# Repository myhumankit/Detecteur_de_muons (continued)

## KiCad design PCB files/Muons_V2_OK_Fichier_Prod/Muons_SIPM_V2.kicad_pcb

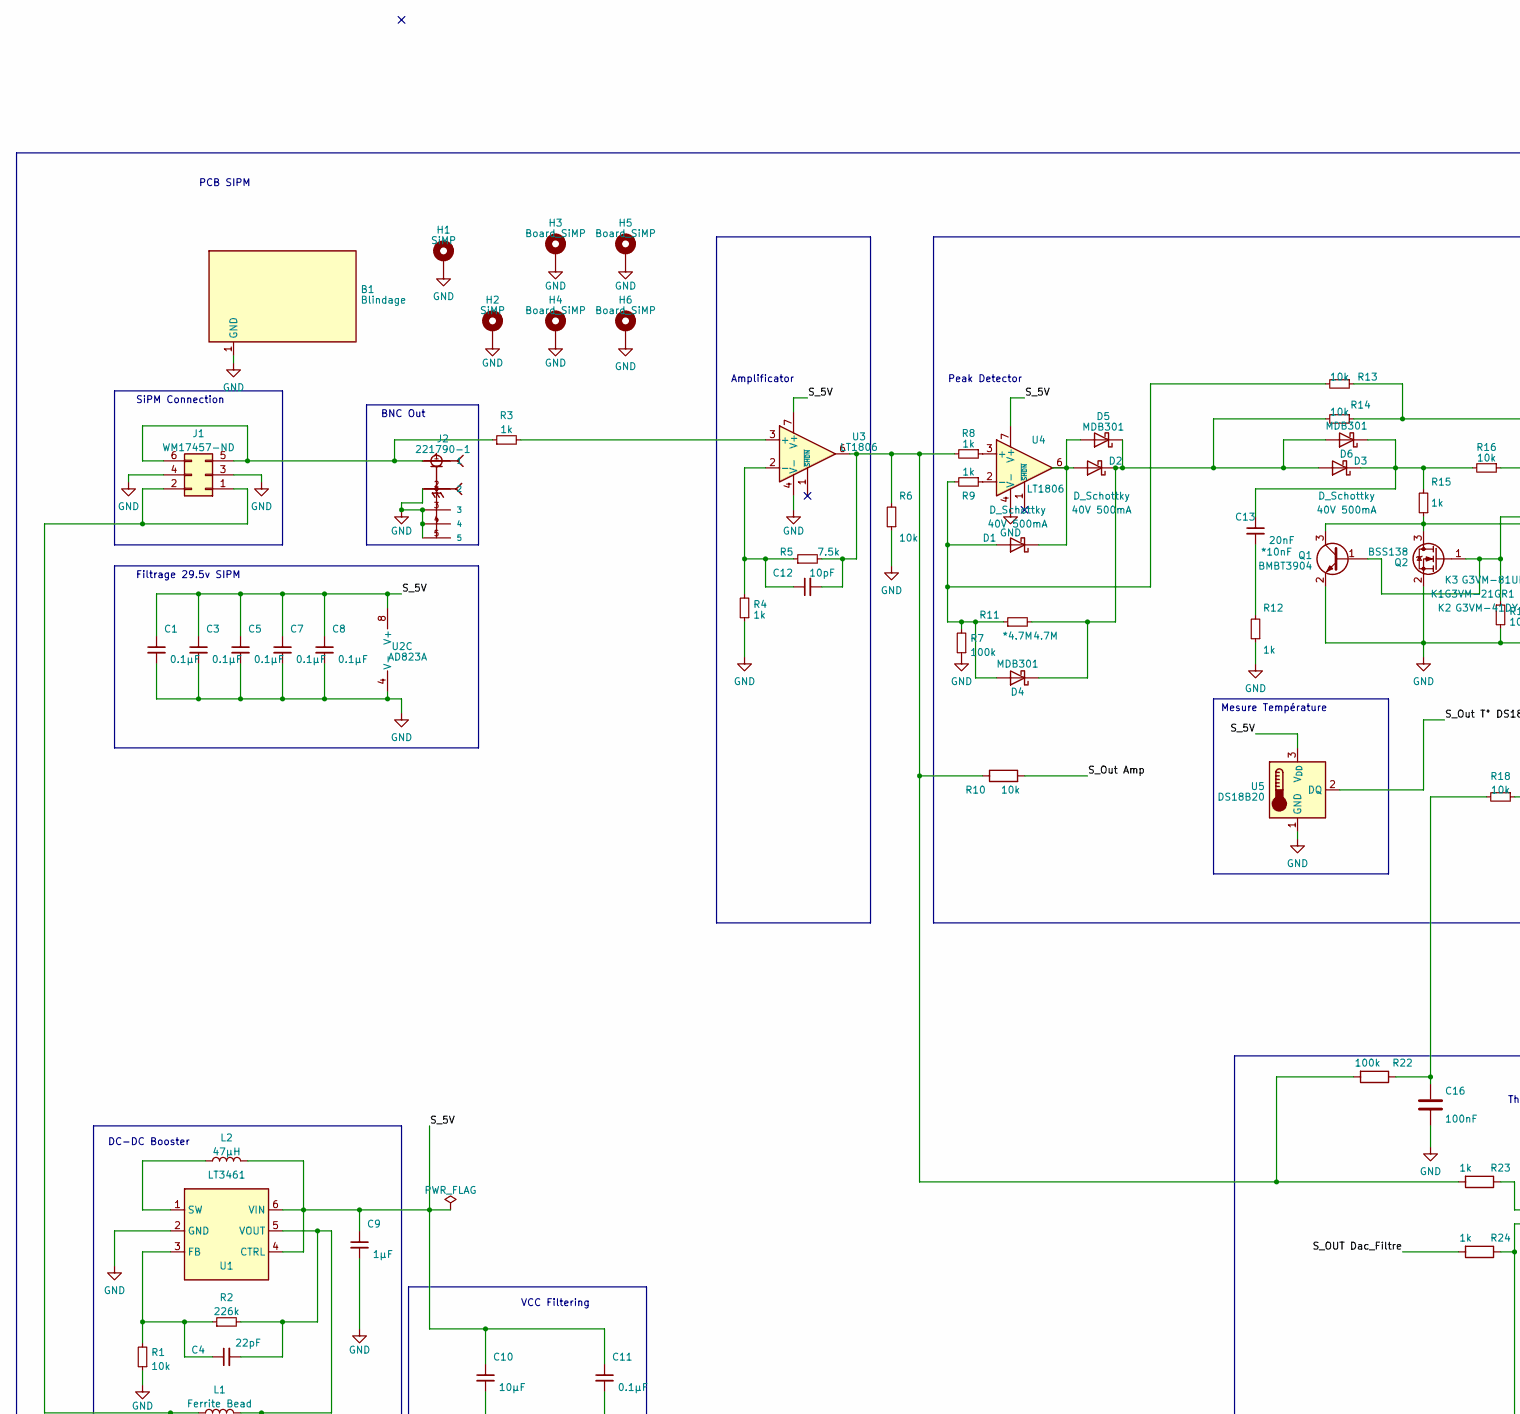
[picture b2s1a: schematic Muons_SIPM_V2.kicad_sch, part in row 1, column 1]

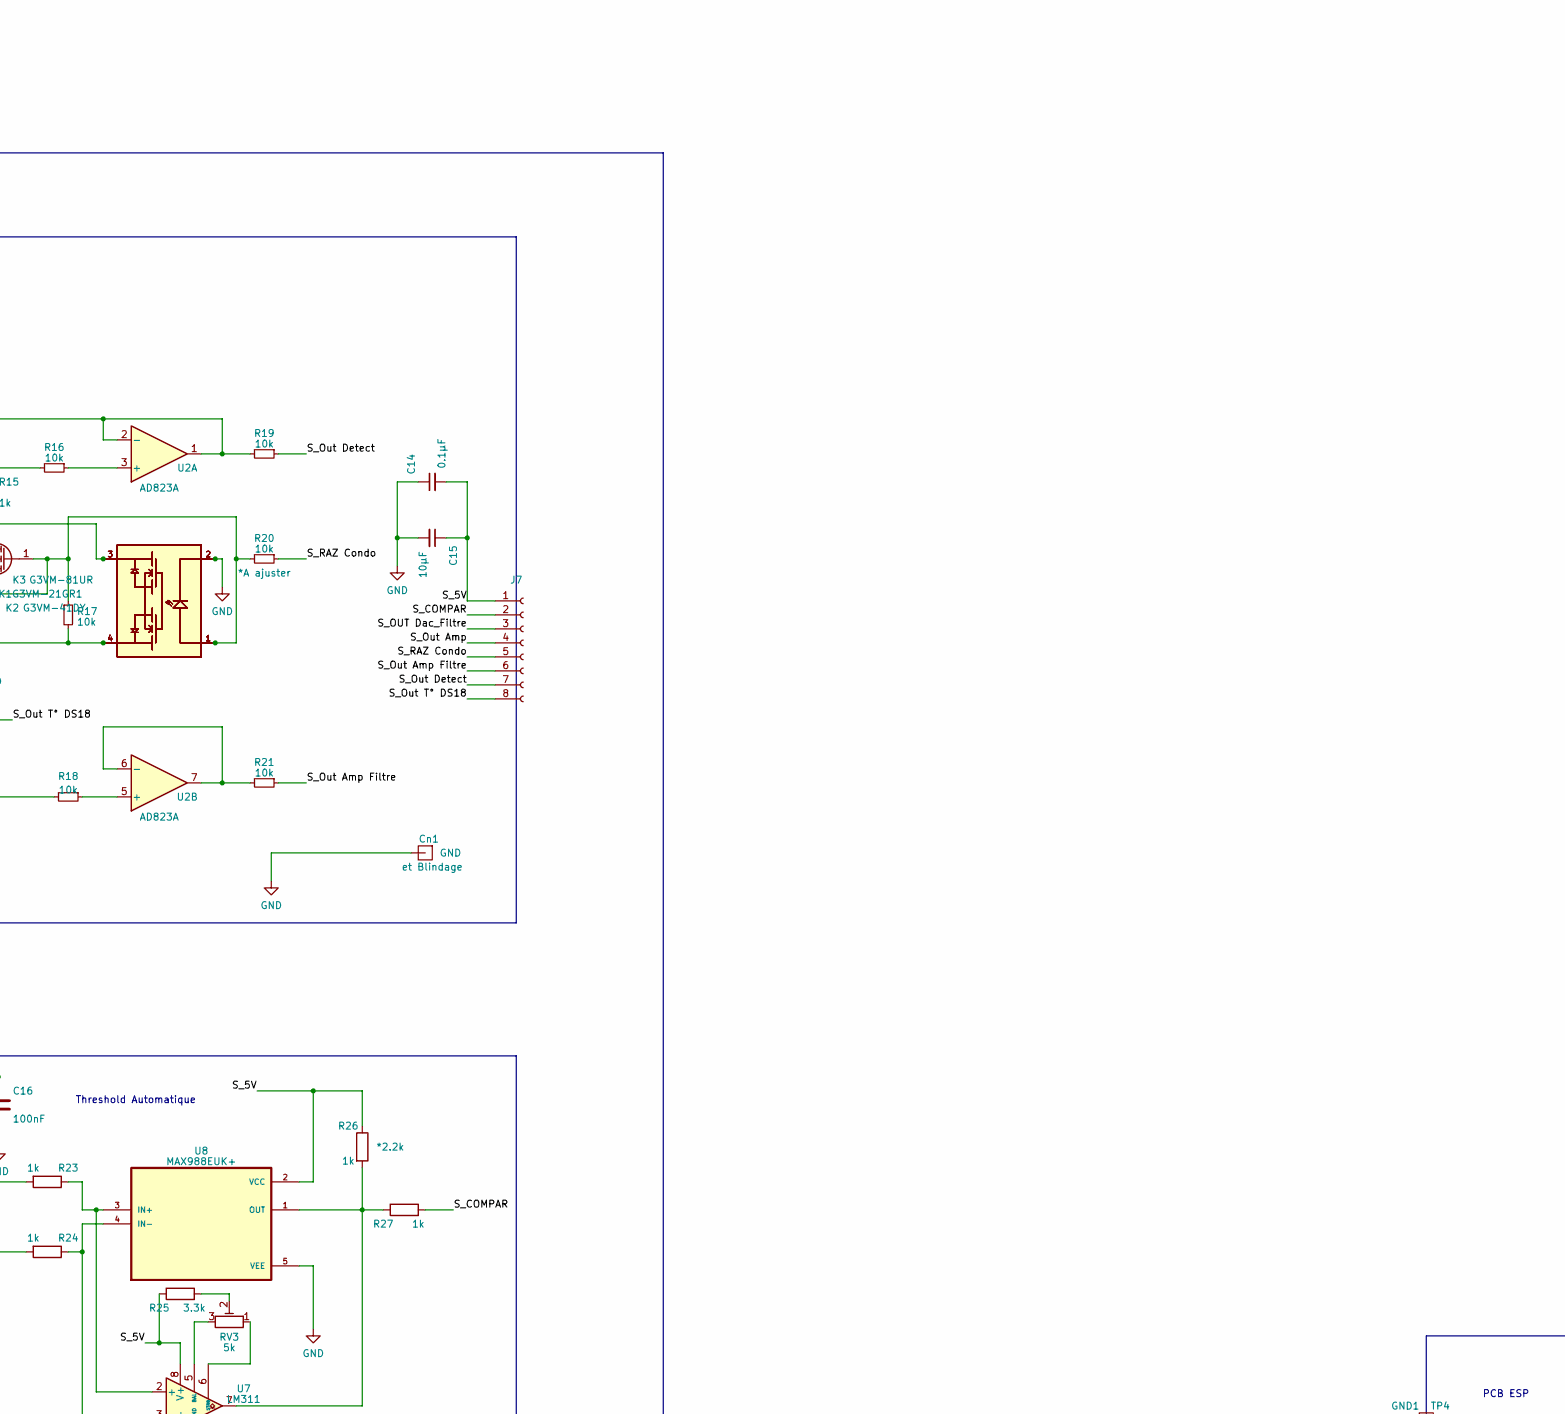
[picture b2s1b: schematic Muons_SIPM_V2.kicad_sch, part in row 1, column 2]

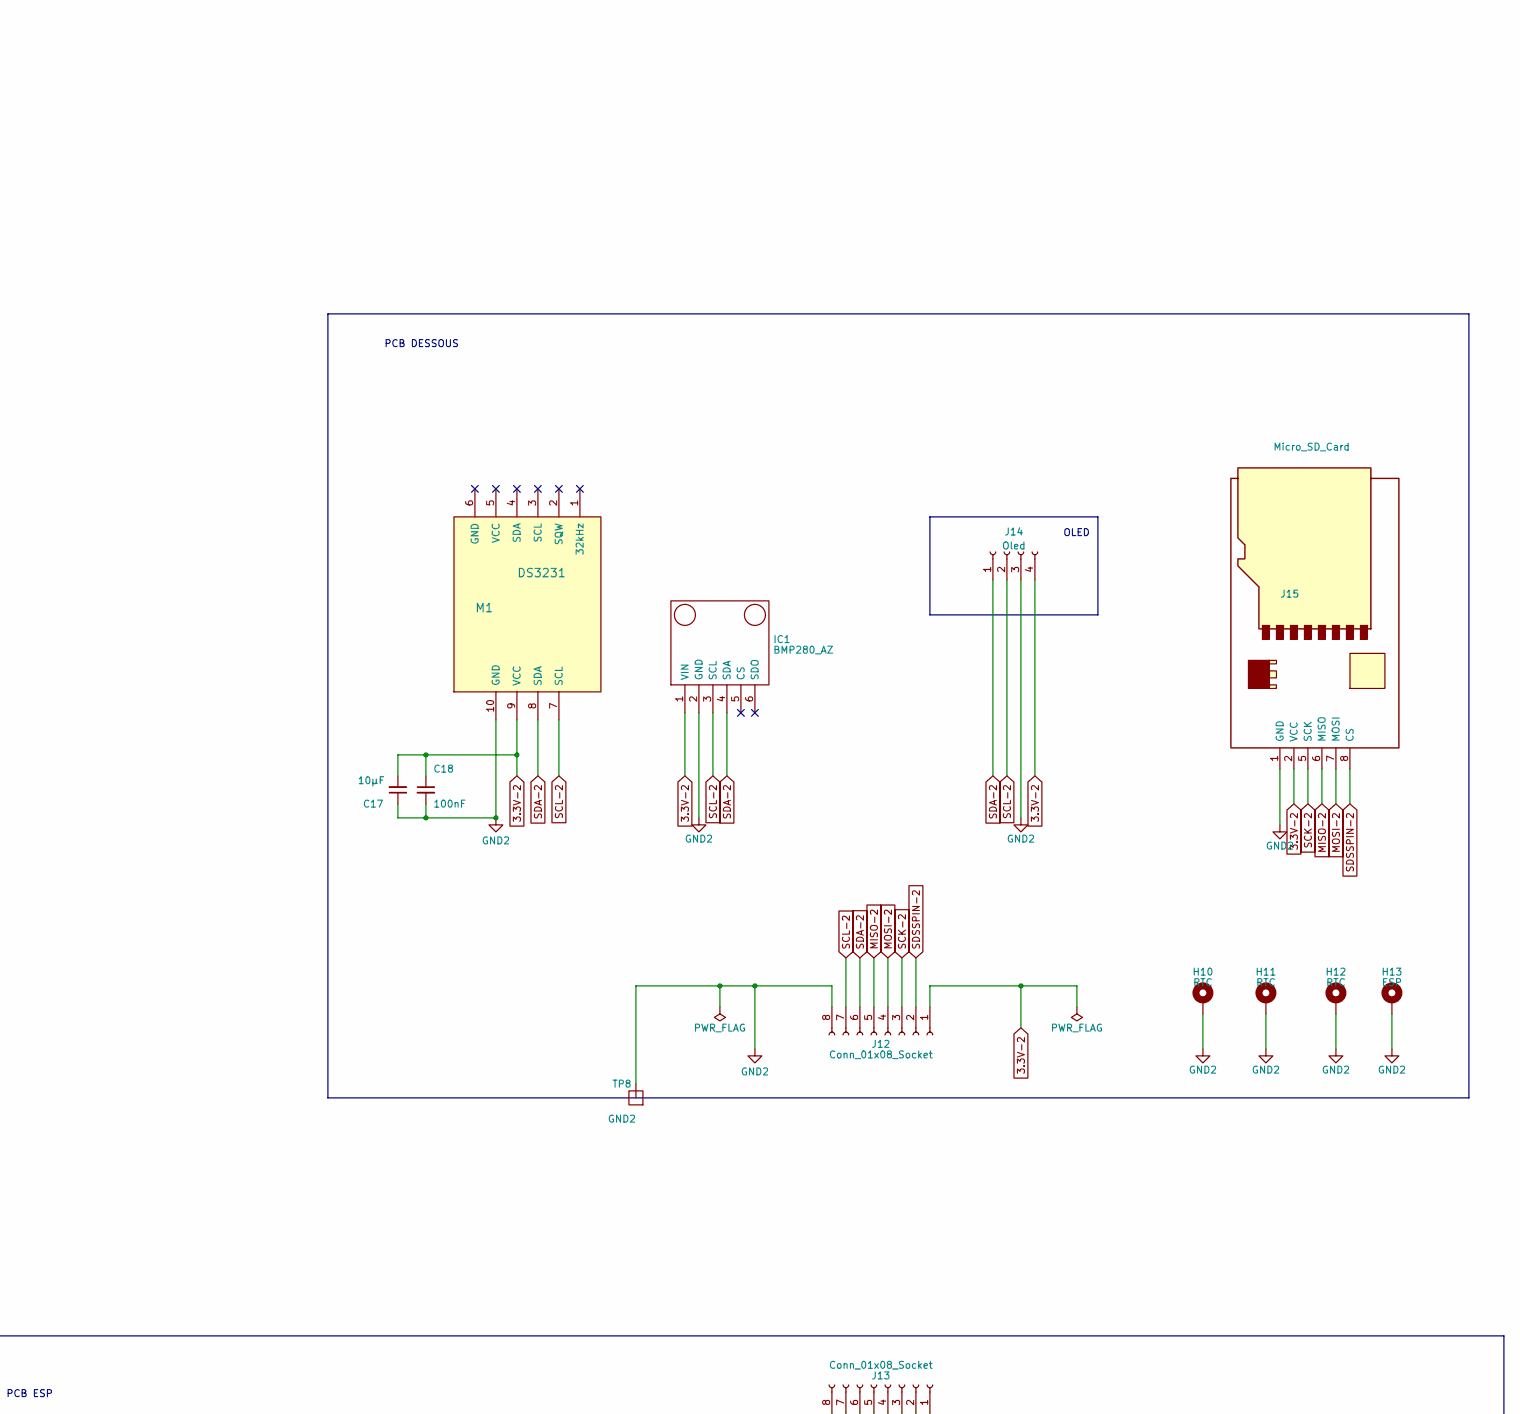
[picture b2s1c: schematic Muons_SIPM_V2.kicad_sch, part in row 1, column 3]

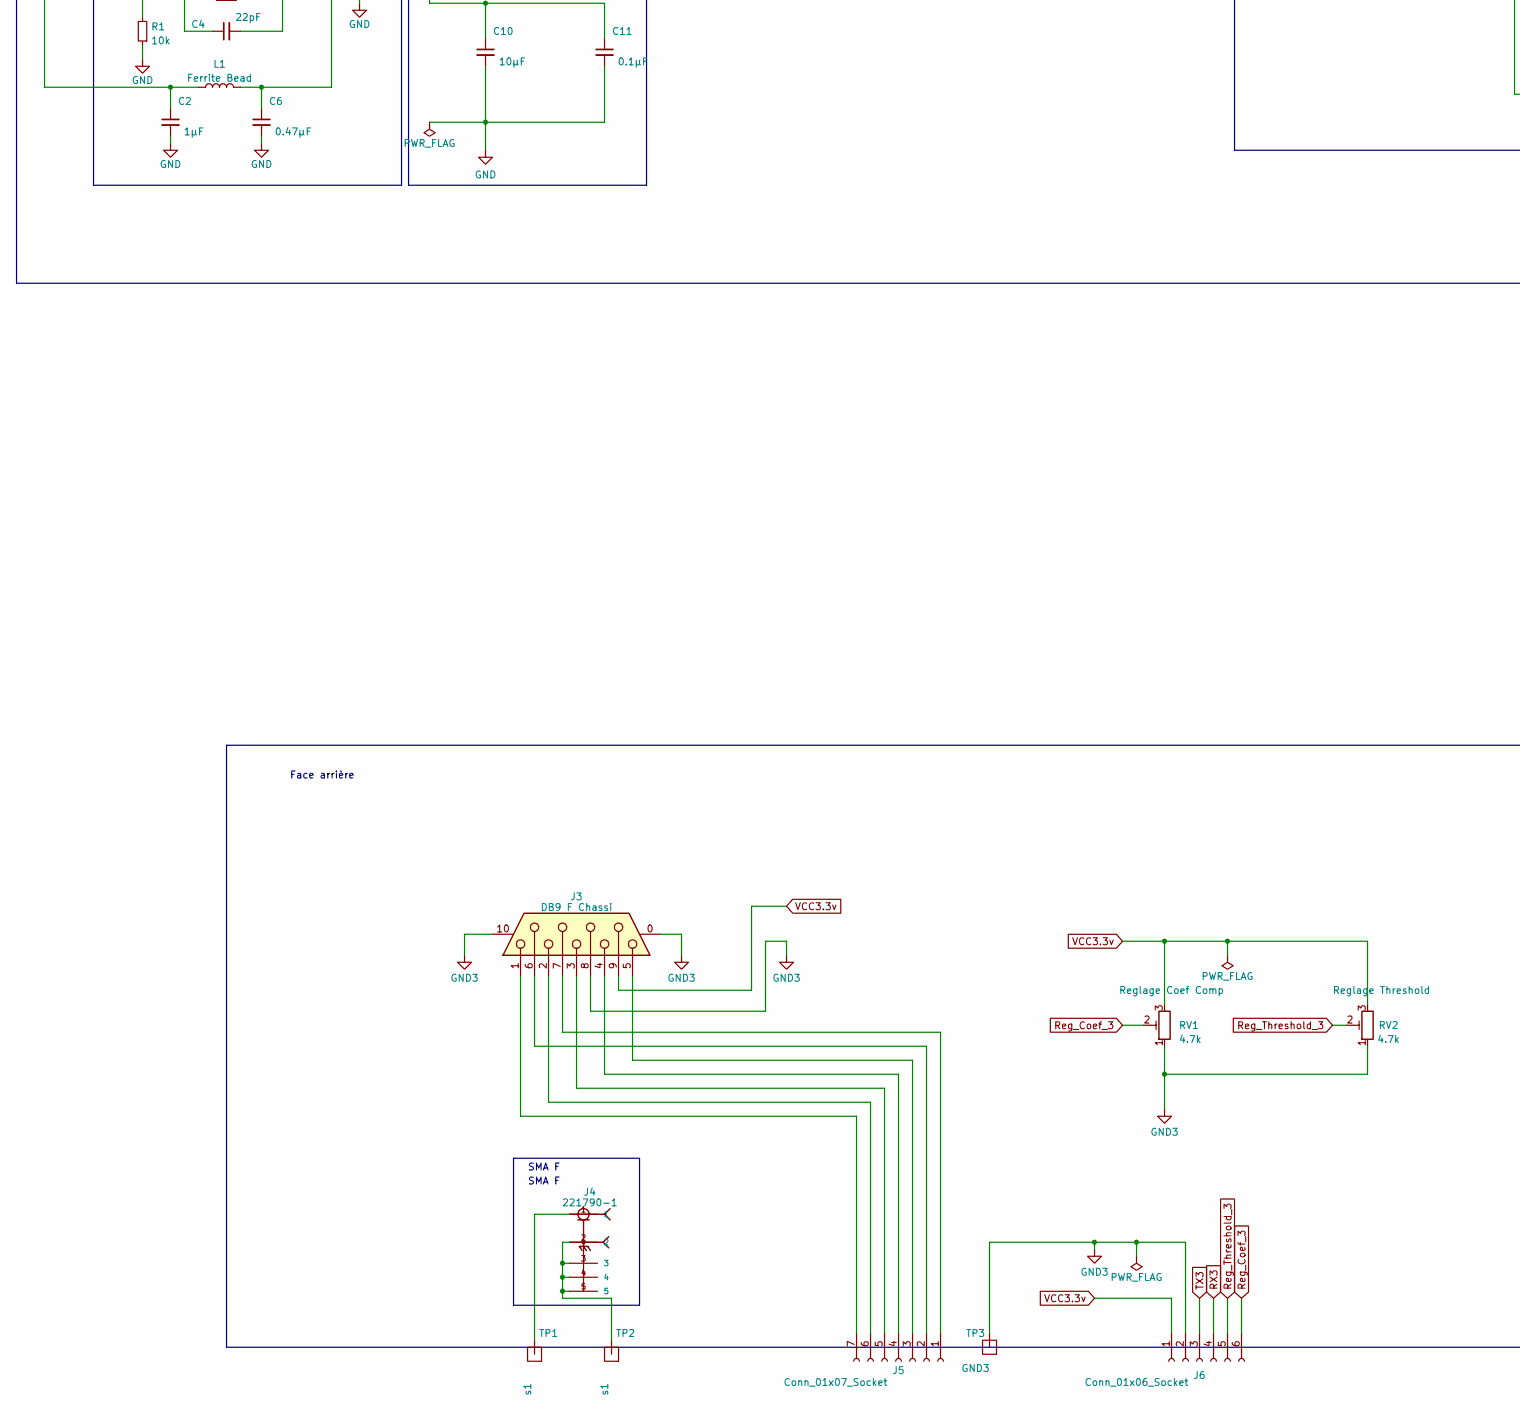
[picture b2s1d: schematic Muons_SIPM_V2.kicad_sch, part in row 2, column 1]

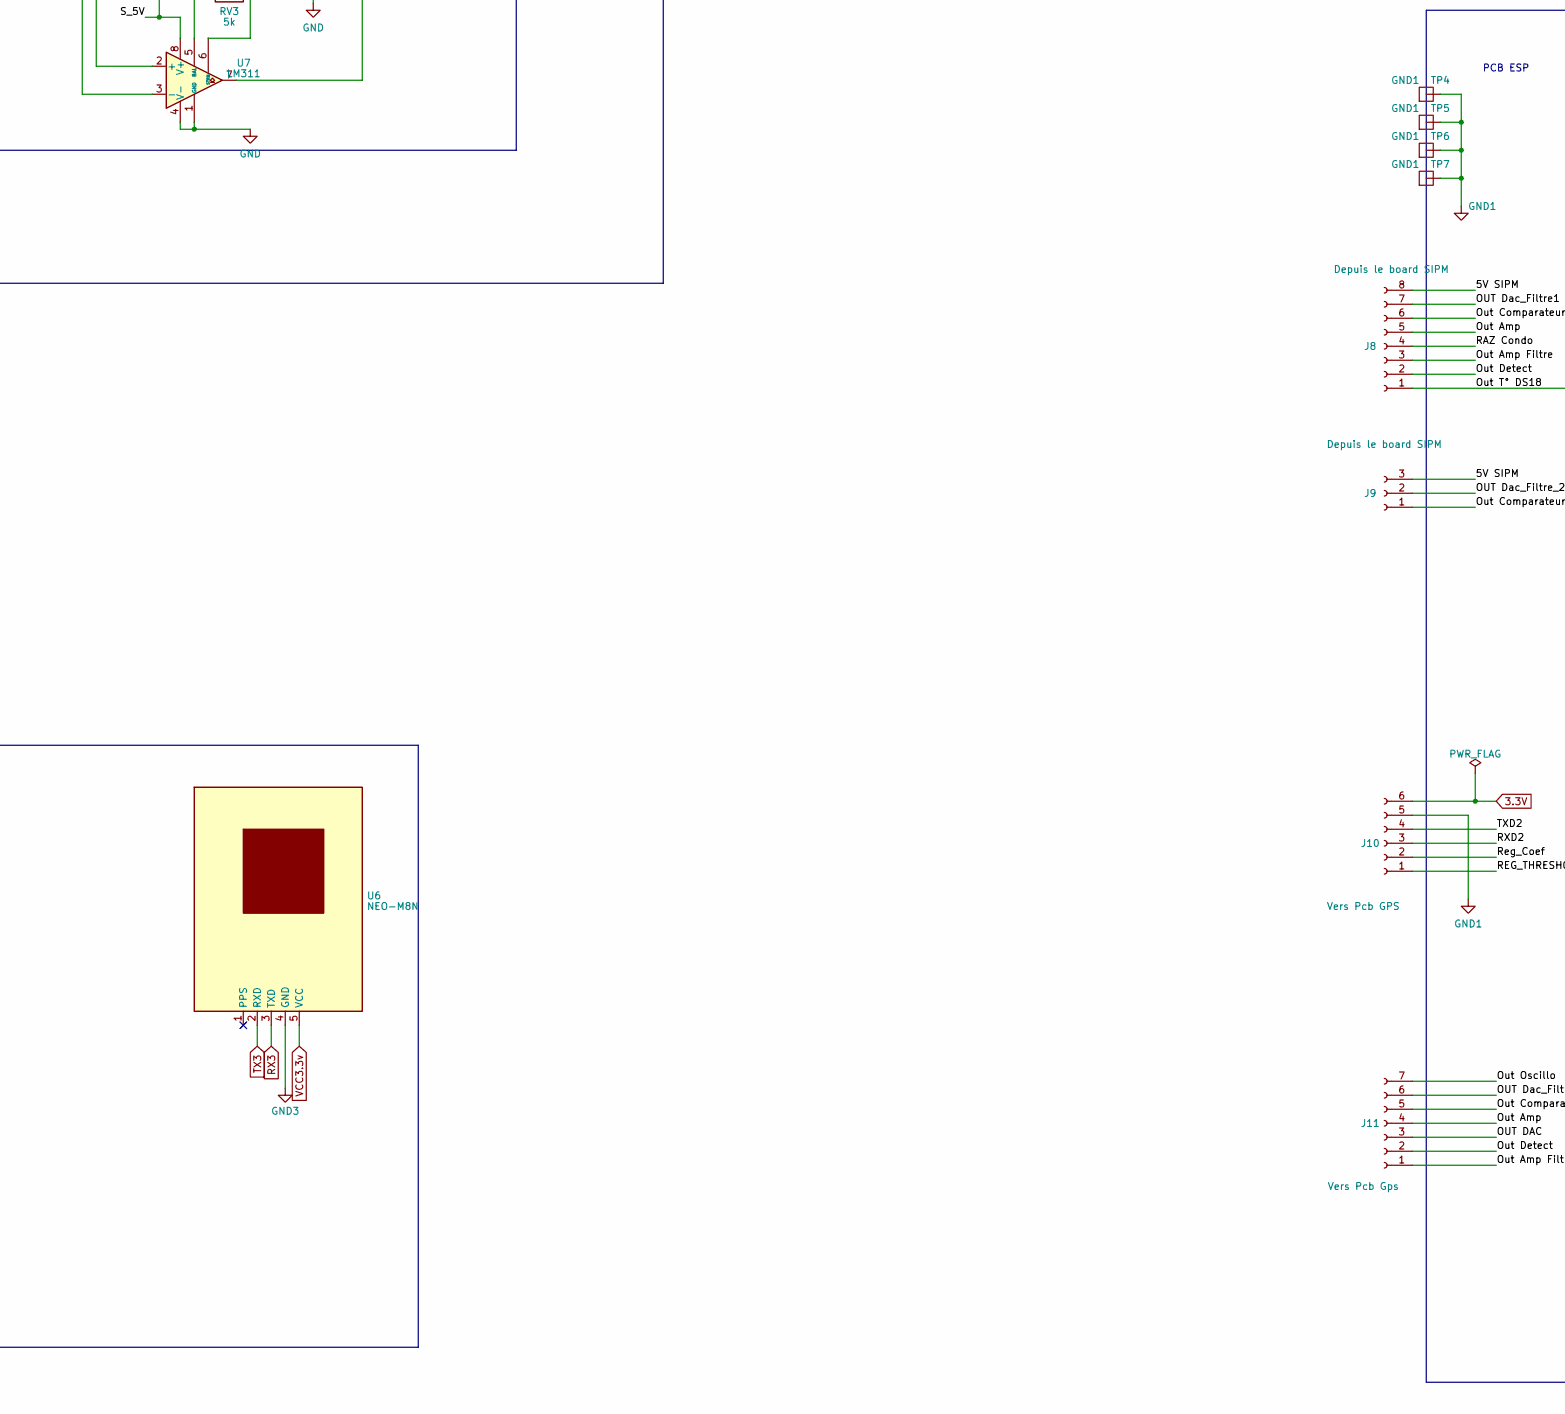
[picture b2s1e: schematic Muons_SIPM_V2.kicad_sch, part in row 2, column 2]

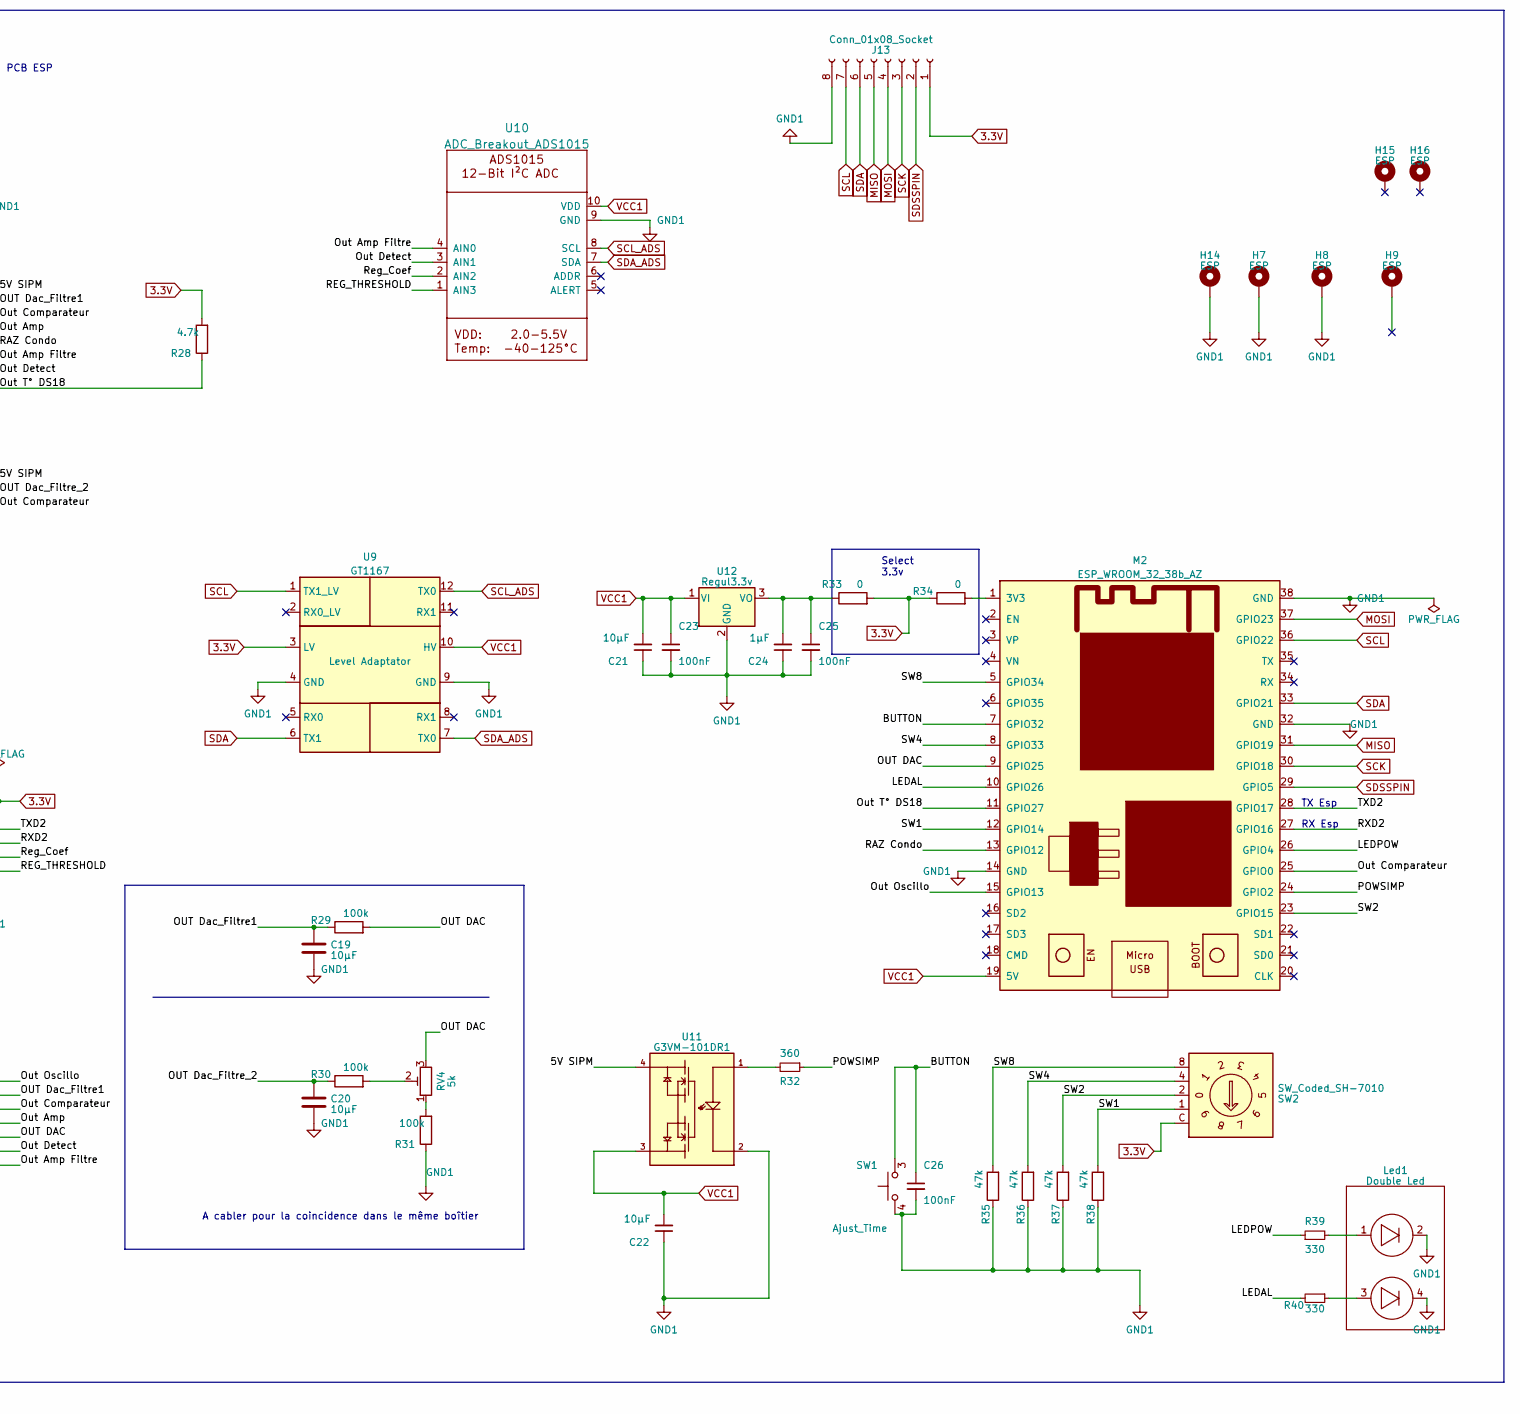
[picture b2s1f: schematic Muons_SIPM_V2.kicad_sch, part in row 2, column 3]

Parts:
B1: Blindage; Blindage_29.5
C1, C3, C5, C7, C8, C11, C14: 0.1µF; C_0805_Muons
C2, C9, C24: 1µF; C_0805_Muons
C4: 22pF; C_0805_Muons
C6: 0.47µF; C_0805_Muons
C10, C15, C17, C19, C20, C21, C22: 10µF; C_0805_Muons
C12: 10pF; C_0805_Muons
C13: 20nF; C_0805_Muons
C16, C18, C23, C25, C26: 100nF; C_0805_Muons
Cn1: GND; TestPoint_THTPad_4.75x3.7mm_Drill1.5mm
D1, D2, D3: D_Schottky; D_SOD-123
D4, D5, D6: MDB301; SOT-23
H1, H2: SiMP; MountingHole_2.2mm_M2_DIN965_Pad_TopBottom
H3, H4, H5, H6: Board_SiMP; MountingHole_2.2mm_M2_DIN965_Pad_TopBottom
H7, H8, H9, H13, H14: ESP; MountingHole_2.2mm_M2_DIN965_Pad_TopBottom
H10, H11, H12: RTC; MountingHole_2.2mm_M2_DIN965_Pad_TopBottom
H15, H16: ESP; MountingHole_2.2mm_M2
IC1: BMP280_AZ; Manufacturer_Part_Number BMP280_AZ
J1: WM17457-ND; PinSocket_2x03_P2.54mm_Vertical
J2, J4: 221790-1; TE_221790-1
J3: DB9 F Chassi; DSUB-9_Female_Horizontal_P2.77x2.84mm_EdgePinOffset4.94mm_H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
J5: Conn_01x07_Socket; Molex_KK-254_AE-6410-07A_1x07_P2.54mm_Vertical
J6: Conn_01x06_Socket; Molex_KK-254_AE-6410-06A_1x06_P2.54mm_Vertical
J7: Conn_01x08_Socket; Molex_KK-254_AE-6410-08A_1x08_P2.54mm_Vertical
J8: Depuis le board SIPM; Molex_KK-254_AE-6410-08A_1x08_P2.54mm_Vertical
J9: Depuis le board SIPM; Molex_KK-254_AE-6410-03A_1x03_P2.54mm_Vertical
J10: Vers Pcb GPS; Molex_KK-254_AE-6410-06A_1x06_P2.54mm_Vertical
J11: Vers Pcb Gps; Molex_KK-254_AE-6410-07A_1x07_P2.54mm_Vertical
J12: Conn_01x08_Socket; PinSocket_1x08_P2.54mm_Vertical
J13: Conn_01x08_Socket; PinHeader_1x08_P2.54mm_Vertical
J14: Oled; OLED_PCB
J15: Micro_SD_Card; SD-CARD_AZ
K1: G3VM-21GR1; PARTREV 0215
K2: G3VM-41DY; RELAY_G3VM-41DY; PARTREV 0215
K3: G3VM-81UR; PARTREV 0215
L1: Ferrite Bead; R_0805_2012Metric_Pad1.20x1.40mm_HandSolder
L2: 47µH; R_1210_3225Metric_Pad1.30x2.65mm_HandSolder
Led1: Double Led; Double_Led
M1: DS3231; REG_DS3231_2023
M2: ESP_WROOM_32_38b_AZ; MODULE_ESP32-DEVKITC
Q1: BMBT3904; SOT-323_SC-70
Q2: BSS138; SOT-23
R1, R6, R10, R13, R14, R16, R17, R18, R19, R20, R21: 10k; R_0805_Muons
R2: 226k; R_0805_Muons
R3, R4, R8, R9, R12, R15, R23, R24, R26, R27: 1k; R_0805_Muons
R5: 7.5k; R_0805_Muons
R7, R22, R29, R30, R31: 100k; R_0805_Muons
R11: 4.7M; R_0805_Muons
R25: 3.3k; R_0805_Muons
R28: 4.7k; R_0805_Muons
R32: 360; R_0805_Muons
R33, R34: 0; R_Shunt_0805_Muons
R35, R36, R37, R38: 47k; R_0805_Muons
R39, R40: 330; R_0805_Muons
RV1, RV2: 4.7k; Potentiometer_Bourns_3005_Horizontal
RV3, RV4: 5k; Potentiometer_Bourns_3314G_Vertical
SW1: Ajust_Time; SW_Tactile_SPST_Angled_PTS645Vx83-2LFS
SW2: SW_Coded_SH-7010; Nidec_Copal_SC-1110
TP1, TP2: s1; TestPoint_THTPad_4.75x3.7mm_Drill1.5mm
TP3: GND3; TestPoint_THTPad_4.75x3.7mm_Drill1.5mm
TP4, TP5, TP6, TP7: GND1; TestPoint_THTPad_4.75x3.7mm_Drill1.5mm
TP8: GND2; TestPoint_THTPad_4.75x3.7mm_Drill1.5mm
U1: LT3461; TSOT-23-6
U2: AD823A; SOIC-8_3.9x4.9mm_P1.27mm
U3, U4: LT1806; SOIC-8_3.9x4.9mm_P1.27mm
U5: DS18B20; TO-92_Inline
U6: NEO-M8N; GPS_NEO8
U7: LM311; SOIC-8_3.9x4.9mm_P1.27mm
U8: MAX988EUK+; SOT95P280X145-5N
U9: GT1167; DIP-12_Convertisseur
U10: ADC_Breakout_ADS1015; ADS1115_Small_BreakBord
U11: G3VM-101DR1; G3VM-21GR1; PARTREV 0215
U12: Regul3.3v; Regulateur

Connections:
3.3V: J10.6, J13.1, R28.2, R33.2, R34.1, SW2.C, U9.3 (LV)
3.3V-2: C17.2, C18.1, IC1.1 (VIN), J12.1, J14.4, J15.2 (VCC), M1.9 (VCC)
/5V SIPM: J8.8, J9.3, U11.4
/BUTTON: C26.1, M2.7 (GPIO32), SW1.3 (B), SW1.4 (B)
/LEDAL: M2.10 (GPIO26), R40.2
/LEDPOW: M2.26 (GPIO4), R39.1
/OUT DAC: J11.3, M2.9 (GPIO25), R29.2, RV4.3
/OUT Dac_Filtre1: C19.1, J8.7, J11.6, R29.1
/OUT Dac_Filtre_2: C20.1, J9.2, R30.1
/Out Amp: J8.5, J11.4
/Out Amp Filtre: J8.3, J11.1, U10.4 (AIN0)
/Out Comparateur: J8.6, J9.1, J11.5, M2.25 (GPIO0)
/Out Detect: J8.2, J11.2, U10.3 (AIN1)
/Out Oscillo: J11.7, M2.15 (GPIO13)
/Out T° DS18: J8.1, M2.11 (GPIO27), R28.1
/POWSIMP: M2.24 (GPIO2), R32.1
/RAZ Condo: J8.4, M2.13 (GPIO12)
/REG_THRESHOLD: J10.1, U10.1 (AIN3)
/RXD2: J10.3, M2.27 (GPIO16)
/Reg_Coef: J10.2, U10.2 (AIN2)
/SW1: M2.12 (GPIO14), R38.2, SW2.1
/SW2: M2.23 (GPIO15), R37.2, SW2.2
/SW4: M2.8 (GPIO33), R36.2, SW2.4
/SW8: M2.5 (GPIO34), R35.2, SW2.8
/S_5V: C1.1, C3.1, C5.1, C7.1, C8.1, C9.1, C10.1, C11.1, C14.2, C15.1, J7.1, L2.2, R25.1, R26.1, U1.4 (CTRL), U1.6 (VIN), U2.8 (V+), U3.7 (V+), U4.7 (V+), U5.3 (V_{DD}), U7.8 (V+), U8.2 (VCC)
/S_COMPAR: J7.2, R27.2
/S_OUT Dac_Filtre: J7.3, R24.2
/S_Out Amp: J7.4, R10.2
/S_Out Amp Filtre: J7.6, R21.1
/S_Out Detect: J7.7, R19.1
/S_Out T° DS18: J7.8, U5.2 (DQ)
/S_RAZ Condo: J7.5, R20.1
/TXD2: J10.4, M2.28 (GPIO17)
GND: B1.1 (GND), C1.2, C2.2, C3.2, C5.2, C6.2, C7.2, C8.2, C9.2, C10.2, C11.2, C14.1, C15.2, C16.2, Cn1.1, H1.1, H2.1, H3.1, H4.1, H5.1, H6.1, J1.3, J1.4, J2.2, J2.3, J2.4, J2.5, K1.2, K1.4, K2.2, K2.4, K3.2, K3.4, Q1.2 (E), Q2.2 (S), R1.1, R4.1, R6.1, R7.1, R12.1, R17.2, U1.2 (GND), U2.4 (V-), U3.4 (V-), U4.4 (V-), U5.1 (GND), U7.1 (GND), U7.4 (V-), U8.5 (VEE)
GND1: C19.2, C20.2, C21.1, C22.1, C23.2, C24.1, C25.2, C26.2, H7.1, H8.1, H14.1, J10.5, J13.8, Led1.2 (K1), Led1.4 (K2), M2.14 (GND), M2.32 (GND), M2.38 (GND), R31.1, R35.1, R36.1, R37.1, R38.1, SW1.1 (A), SW1.2 (A), TP4.1, TP5.1, TP6.1, TP7.1, U9.4 (GND), U9.9 (GND), U10.9 (GND), U11.2, U12.2 (GND)
GND2: C17.1, C18.2, H10.1, H11.1, H12.1, H13.1, IC1.2 (GND), J12.8, J14.3, J15.1 (GND), M1.10 (GND), TP8.1
GND3: J3.0 (PAD), J3.8, J3.10 (PAD), J6.2, RV1.1, RV2.1, TP3.1, U6.4 (GND)
MISO: J13.5, M2.31 (GPIO19)
MISO-2: J12.5, J15.6 (MISO)
MOSI: J13.4, M2.37 (GPIO23)
MOSI-2: J12.4, J15.7 (MOSI)
unnamed: C12.2, R5.2, R6.2, R8.2, R10.1, R22.2, R23.2, U3.6
unnamed: C13.2, R12.2
unnamed: C16.1, R18.2, R22.1
unnamed: D1.2 (A), D4.1 (A), R7.2, R9.2, R11.1, R13.2
unnamed: D1.1 (K), D2.2 (A), D5.1 (A), U4.6
unnamed: D2.1 (K), D3.2 (A), D4.3 (K), D5.3 (K), D6.1 (A), R11.2, R14.2
unnamed: C13.1, D3.1 (K), D6.3 (K), R15.2, R16.2
unnamed: C2.1, J1.1, J1.2, L1.1
unnamed: J1.5, J1.6, J2.1, R3.1
unnamed: J4.1, TP1.1
unnamed: J4.2, J4.3, J4.4, J4.5, TP2.1
unnamed: J3.7, J5.1
unnamed: J3.6, J5.2
unnamed: J3.5, J5.3
unnamed: J3.4, J5.4
unnamed: J3.3, J5.5
unnamed: J3.2, J5.6
unnamed: J3.1, J5.7
unnamed: Led1.1 (A1), R39.2
unnamed: Led1.3 (A2), R40.1
unnamed: M2.1 (3V3), R34.2
unnamed: K1.1, K2.1, K3.1, Q1.1 (B), Q2.1 (G), R17.1, R20.2
unnamed: K1.3, K2.3, K3.3, Q1.3 (C), Q2.3 (D), R15.1
unnamed: R25.2, RV3.2
unnamed: R30.2, RV4.2
unnamed: R31.2, RV4.1
unnamed: R32.2, U11.1
unnamed: C4.1, R1.2, R2.1, U1.3 (FB)
unnamed: L2.1, U1.1 (SW)
unnamed: C4.2, C6.1, L1.2, R2.2, U1.5 (VOUT)
unnamed: R16.1, U2.3 (+)
unnamed: R13.1, R14.1, R19.2, U2.1, U2.2 (-)
unnamed: R18.1, U2.5 (+)
unnamed: R21.2, U2.6 (-), U2.7
unnamed: R3.2, U3.3 (+)
unnamed: C12.1, R4.2, R5.1, U3.2 (-)
unnamed: R8.1, U4.3 (+)
unnamed: R9.1, U4.2 (-)
unnamed: R23.1, U7.2 (+), U8.3 (IN+)
unnamed: R24.1, U7.3 (-), U8.4 (IN-)
unnamed: RV3.3, U7.5 (BAL)
unnamed: RV3.1, U7.6 (STRB)
unnamed: R26.2, R27.1, U7.7, U8.1 (OUT)
unnamed: C24.2, C25.1, R33.1, U12.3 (VO)
RX3: J6.4, U6.3 (TXD)
Reg_Coef_3: J6.6, RV1.2
Reg_Threshold_3: J6.5, RV2.2
SCK: J13.3, M2.30 (GPIO18)
SCK-2: J12.3, J15.5 (SCK)
SCL: J13.7, M2.36 (GPIO22), U9.1 (TX1_LV)
SCL-2: IC1.3 (SCL), J12.7, J14.2, M1.7 (SCL)
SCL_ADS: U9.12 (TX0), U10.8 (SCL)
SDA: J13.6, M2.33 (GPIO21), U9.6 (TX1)
SDA-2: IC1.4 (SDA), J12.6, J14.1, M1.8 (SDA)
SDA_ADS: U9.7 (TX0), U10.7 (SDA)
SDSSPIN: J13.2, M2.29 (GPIO5)
SDSSPIN-2: J12.2, J15.8 (CS)
TX3: J6.3, U6.2 (RXD)
VCC1: C21.2, C22.2, C23.1, M2.19 (5V), U9.10 (HV), U10.10 (VDD), U11.3, U12.1 (VI)
VCC3.3v: J3.9, J6.1, RV1.3, RV2.3, U6.5 (VCC)

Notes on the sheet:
VCC Filtering
Face arrière
Peak Detector
OLED
PCB DESSOUS
Select 3.3v
PCB ESP
A cabler pour la coincidence dans le même boîtier
PCB SIPM
Mesure Température
RX Esp
SMA F
Filtrage 29.5v SIPM
TX Esp
SiPM Connection
DC-DC Booster
Amplificator
Threshold Automatique
BNC Out

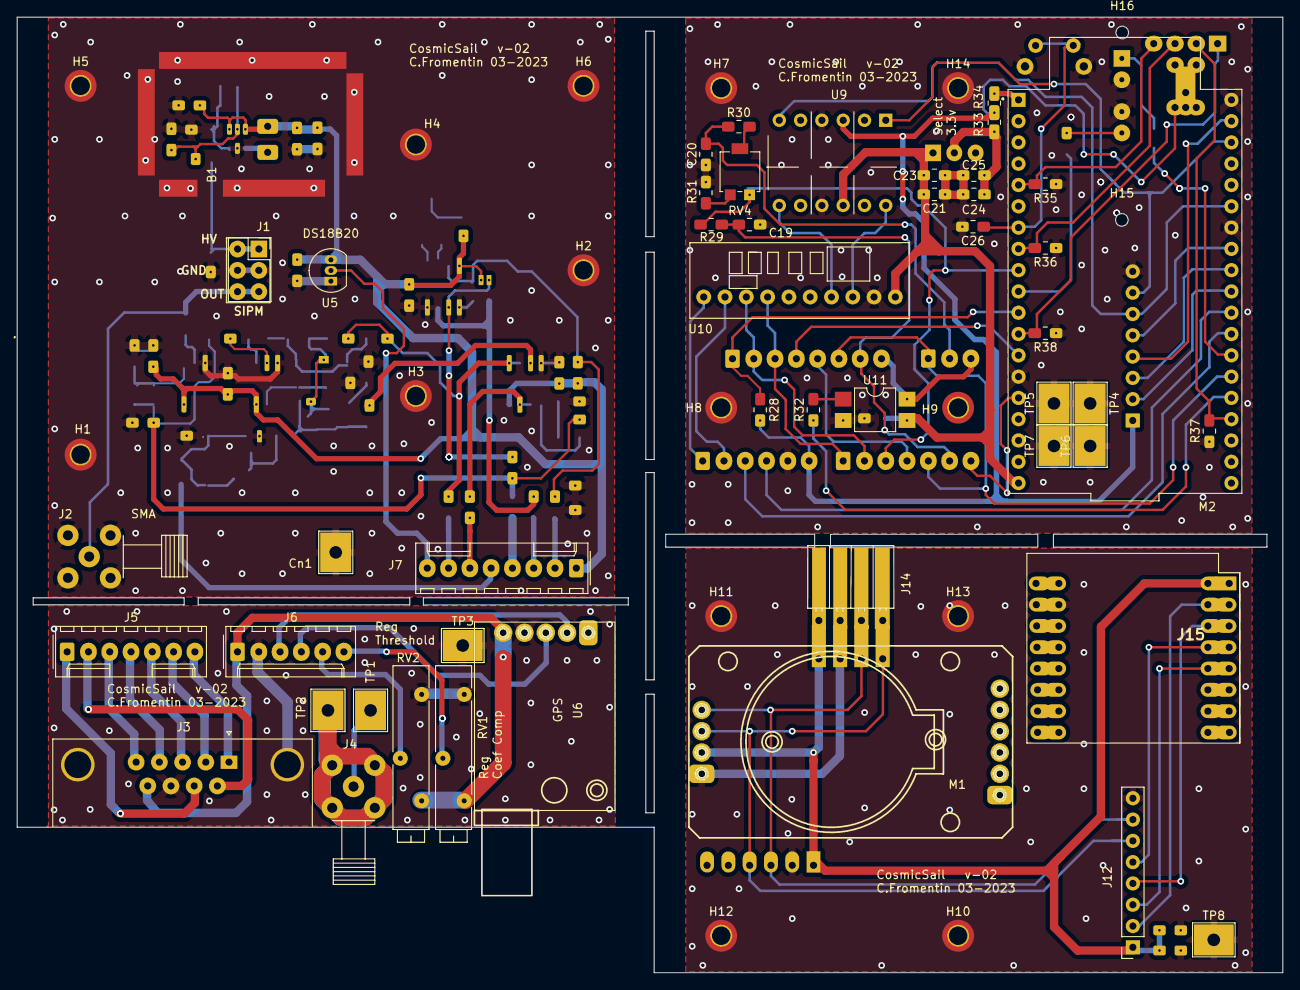
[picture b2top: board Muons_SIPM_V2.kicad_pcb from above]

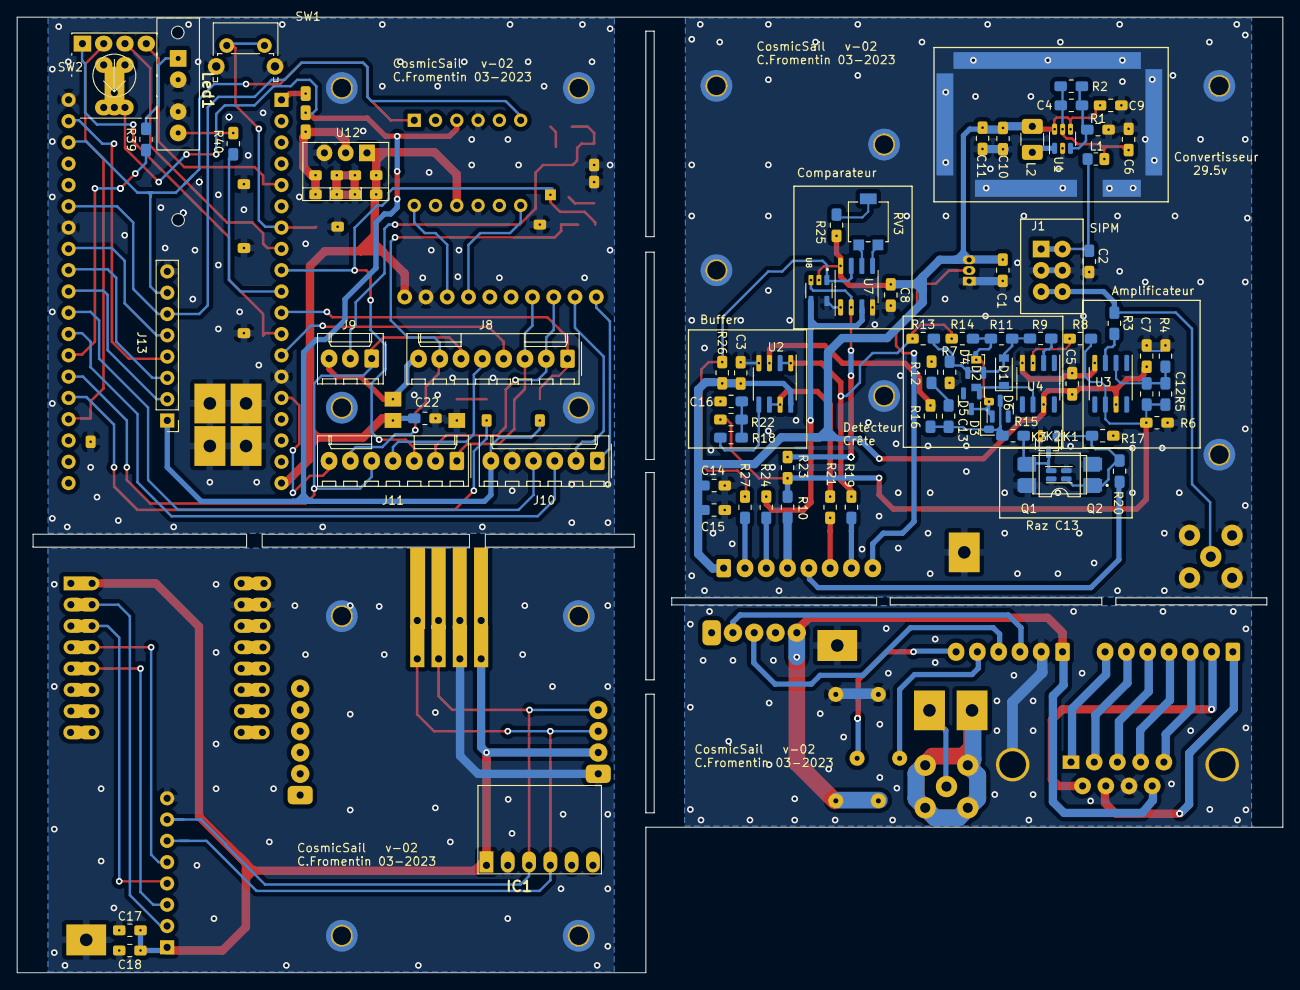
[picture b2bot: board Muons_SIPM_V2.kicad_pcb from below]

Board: 2 copper layers, 151.0 x 114.0 mm, 142 parts (78 on the bottom side), 101 nets.

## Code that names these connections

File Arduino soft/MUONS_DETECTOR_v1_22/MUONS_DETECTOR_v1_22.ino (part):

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
// pins assignement :
#define COMPAR  0        // External Comparator input (interruption)
#define POWSIMP 2        // Powers up the SiPM using an optocoupler
#define LEDPOW  4        // Power led
#define SDSSPIN 5        // SD card CS/SS pin
#define EMPTCAP 12       // relay command to make the SiPM signal drop faster after measurements
#define OSCILLO 13       // ouput for oscilloscope
#define BCDSW4  14       // BCD switch pin 1 (with external pull-down)
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#define RXD2    16       // RXD serial port 2 for communication with GPS
#define TXD2    17       // TXD serial port 2 for communication with GPS
#define DAC     25       // DAC output sending a voltage corresponding to the background noise
#define LEDAL   26       // Alarm led (red)
#define SCITMP  27       // Scintillator temperature
#define BUTTON  32       // Button to adjust RTC timer or close file or ...
#define BCDSW2  33       // BCD switch pin 3 (with external pull-down)
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void setup() {  
  Serial.begin(115200);             
  pinMode(OSCILLO, OUTPUT);        // output for oscillo display
  pinMode(POWSIMP, OUTPUT);        // output to powers up the SiMP
  pinMode(BCDSW1, INPUT);          // set BCD switch pin1 on low (external pull-down)
  pinMode(BCDSW2, INPUT);          // set BCD switch pin2 on low (external pull-down)
  pinMode(BCDSW3, INPUT);          // set BCD switch pin3 on low (external pull-down)
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  u8g2.begin();                    // screen initialization    
  u8g2.enableUTF8Print();          // allow accented characters       

  if (!SD.begin(SDSSPIN))  {       // Check for the presence of an SD card
    messerr = "Card inserted ?";
    ErrorSD();                     // show error message
  }
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  BME280.begin(0x76);              // start BME280 pressure sensor
  DS18B20.begin();                 // start DS18B20 scintillator temperature sensor

  pinMode(LEDAL, OUTPUT);          // Led alarm
  digitalWrite(LEDAL, LOW);        // turn the alarm LED off
  
  ledcSetup(0, 5000, 8);           // DAC channel 0 at 5kHz on 8 bits
  ledcAttachPin(LEDPOW, 0);        // Channel 0 for power led
  ledcWrite(0, powbrgt);           // turn the power LED on with low brigtness

  vTaskDelay(pdMS_TO_TICKS(500));  // delay 500 ms
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
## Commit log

2024-07-02 version initiale
2024-07-15 readme.txt file update
